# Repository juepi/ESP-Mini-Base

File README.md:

# ESP-Mini-Base
Base PCB ("hat") for ESP boards in WEMOS Mini format created with [KiCad EDA](https://www.kicad.org/). Primarily designed for [WEMOS S2 Mini](https://www.wemos.cc/en/latest/s2/s2_mini.html) and [D1 Mini](https://www.wemos.cc/en/latest/d1/d1_mini.html), might work for others / upcoming boards with a compatible pinout.  
The schematic describes the functionality and options in detail, it is also [available as PDF](pdf/ESP-Mini-Base_v1.0_schematic.pdf).

## Available functionality

The board provides the following functions:

* 3x N-Channel MOSFET drains (20A / 20Vds; no more than 5A recommended)
* 1x AC/DC SSR (48Vpp, 500mA max.)
* 1x Supply switch (5V or 3.3V, 2A max.)
* 2x 4-channel Level shifters to 5V
* 1x ADC attenuator with input selection (3V3 rail, 5V rail or external pin)
* 1x Pushbutton
* 3V3 and 5V I2C Pullups for default I2C pins of S2 and D1 Mini
* 5V LDO linear regulator for power supply up to 12V

The board has been designed in a way to allow you maximum flexibility. Every function needs to be enabled via solder jumpers on the bottom PCB side (for default wiring), or you may wire different IOs to the according pin headers on the board.  
The only exclusion are the 8 IOs wired to the 2 level shifters, which are hard wired and cannot be changed. The IOs have been selected to allow you level-shifted SPI or I2C for both S2 and D1 boards.

## Power Supply

There are several ways to power the board, the following table shows you the options and required configuration (solder jumpers on bottom PCB side):

| Powered by | Short Solder Jumpers | Notes |
| --- | --- | --- |
| 5V/VBUS Pin or USB Port | JP12 | Not recommended for MOSFET usage! At least connect GND wire to J9 if you try to do so|
| "12VDC" through J9 | JP12,JP13 | 5V generated from onboard regulator and supplied to ESP. Supported input voltage range: between 6.25 and 12V|
| 3.3VDC through J9 | none | Use to power ESP directly from LFP battery (in example)|

When powering the board from a LFP cell, you might want to have 5VDC (in example for a LED strip). Mainly for this reason, you have the ability to connect a Boost-converter board to J10. Short the Jumper JP11 and JP10 to 1-2 and you will be able to enable the Boost-converter via IO14 (U2 supply switch).  
Although the installed 5V LDO linear regulator supports up to 26V input voltage, no more than 12V are recommended due to the high power dissipation of the regulator.  

## Note on production data

The production data has been created for [JLCPCB assembly service](https://jlcpcb.com/) using the [Fabrication Toolkit Plugin](https://github.com/bennymeg/JLC-Plugin-for-KiCad). When placing an order, keep in mind that the rotation of several parts (MOSFETs, all ICs, C6) needs to be updated. Cross-check with the KiCAD Layout to verify that all parts will be placed correctly.

## Note on MOSFET usage

If you are switching a device through one of the 3 installed N-Channel MOSFETs, make sure that the switched device does **not have any reference to the input voltage GND** of the ESP-Mini-Base (in example through a data connection like I2C etc.). Chances are high to see magic smoke leaving your setup if you fail to use suitable galvanic isolation (beside the fact that the "switched" device probably won't power off at all)!
The MOSFETs have been tested fine with 5kHz PWM, so they should work for dimming RGB LED strips in example. Keep an eye on the overall current running through the FETs, more than 5A should be tested thoroughly before placing it into production.
  
## Pictures

Assembled ESP-Mini-Base v1.0 top side with S2 Mini  

Rendered view of the bottom side showing I/O and solder jumpers with descriptions.

**Note on I2C Pullup solder-jumpers (3,3 and 5V):** all 3 pins of the jumpers need to be connected with tin solder if you want to enable the pullups.

## ESPHome
Added sample ESPHome YAML config which uses most of the functionality provided by the ESP-Mini-Base. The sample is intended to be used with the `WEMOS S2 Mini` board.  
**Note on first wired flash:** The web based flashing with ESPHome did not work for me with the `WEMOS S2 Mini`. I had to download the compiled binary firmware and then used the [Adafruit WebSerial ESPTool](https://adafruit.github.io/Adafruit_WebSerial_ESPTool/) which managed to flash the ESP board correctly. Subsequent OTA updates worked perfectly well with ESPHome.

## Changelog

### v1.1
- Improved high current traces to MOSFETs
- Improved heat dissipation of LDO converter (IC1)
- Upgraded KiCAD files to version 8
- Set "remove from BoM" flag on all THT parts and solder jumpers

Have fun,  
Juergen

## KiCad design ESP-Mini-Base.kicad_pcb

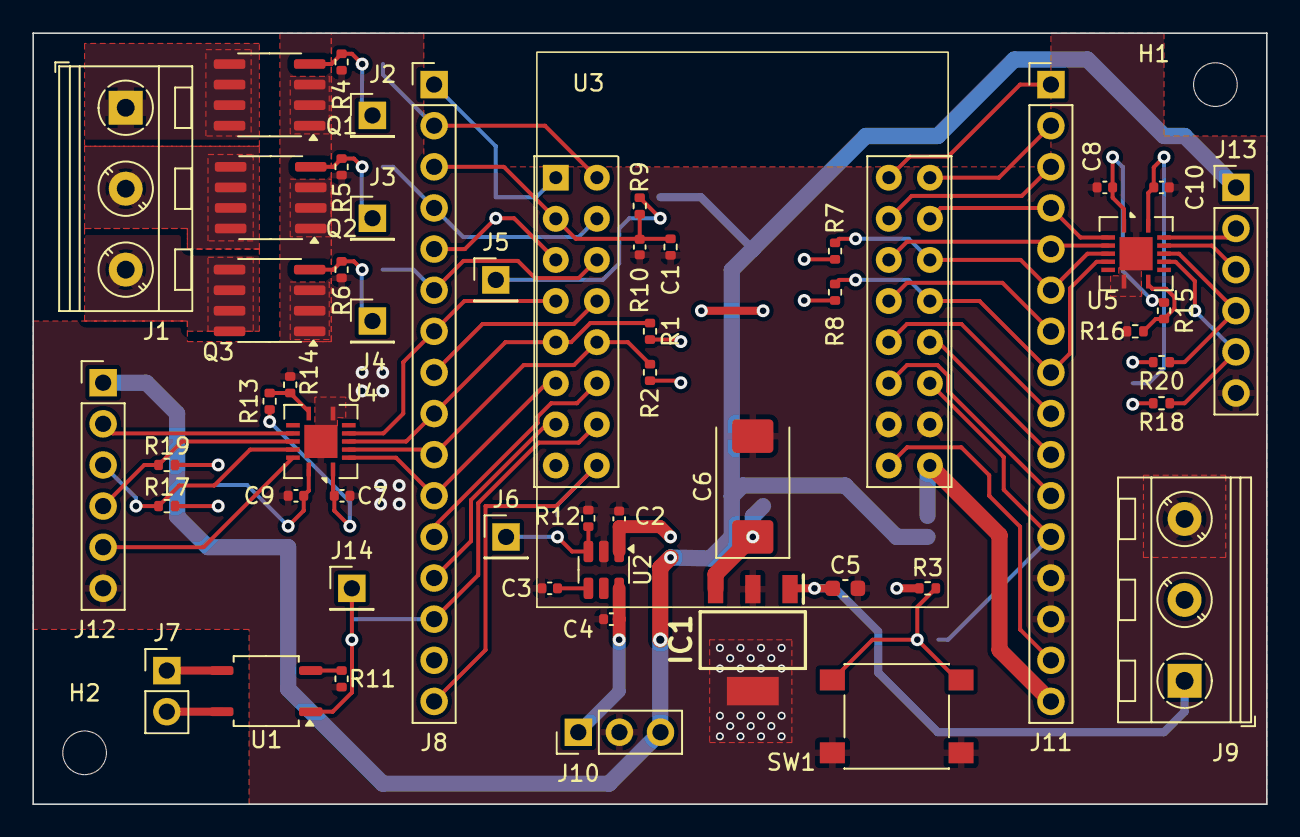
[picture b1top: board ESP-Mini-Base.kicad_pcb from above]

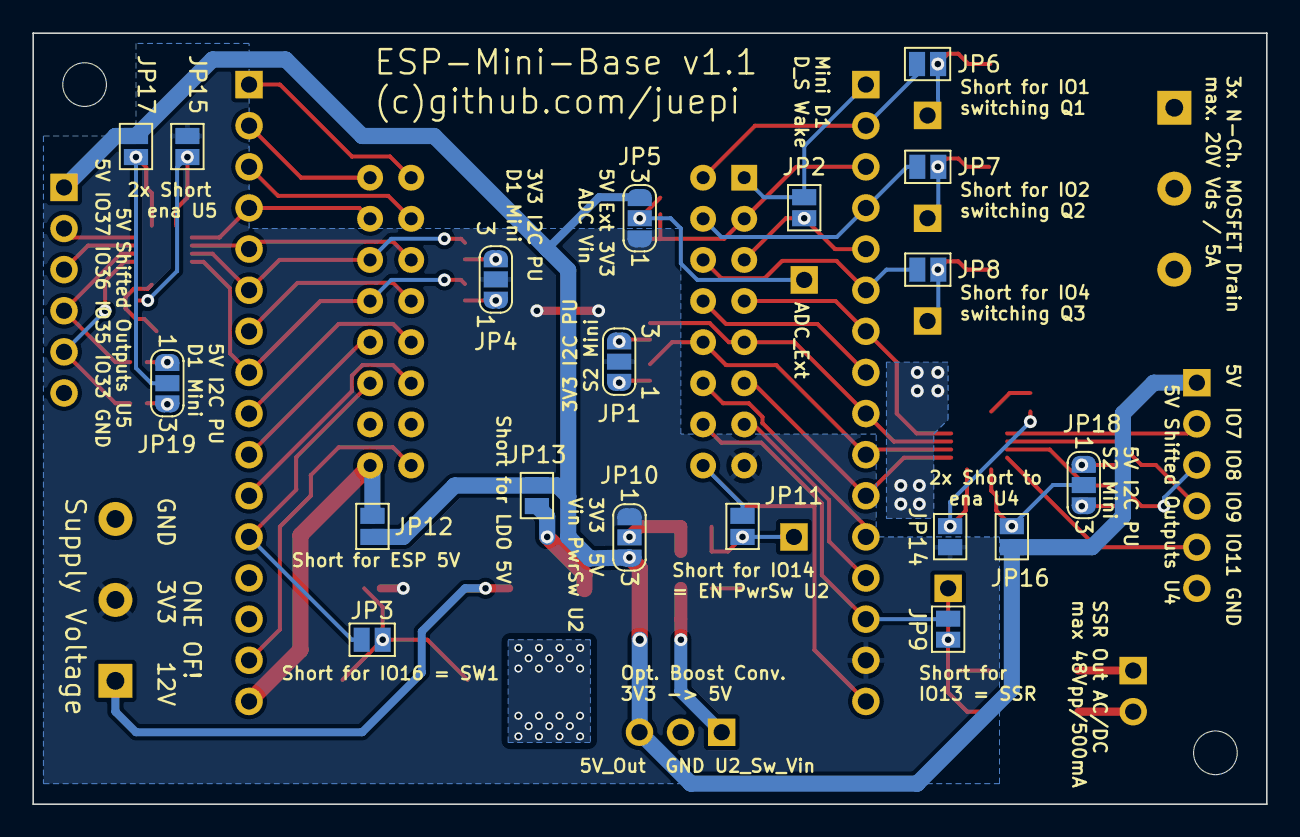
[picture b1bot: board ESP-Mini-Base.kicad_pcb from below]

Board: 2 copper layers, 76.2 x 47.6 mm, 75 parts (19 on the bottom side), 72 nets.

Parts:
C1, C4, C7, C8, C9, C10: 100n/25V; C_0402_1005Metric
C2: 1µ/25V; C_0402_1005Metric
C3: 1n/25V; C_0402_1005Metric
C5: 470nF/50V; C_0603_1608Metric
C6: 100µF/16V; CP_EIA-7343-31_Kemet-D
H1, H2: MountingHole; MountingHole_2.7mm_M2.5
IC1: LM2940IMP-5.0_NOPB; SOT230P700X180-4N
J1, J9: Screw_Terminal_01x03; TerminalBlock_RND_205-00046_1x03_P5.00mm_Horizontal
J2, J3, J4, J5, J6, J14: PinHeader_1x01_P2.54mm_Vertical
J7: Conn_01x02; PinHeader_1x02_P2.54mm_Vertical
J8, J11: Conn_01x16; PinHeader_1x16_P2.54mm_Vertical
J10: Conn_01x03; PinHeader_1x03_P2.54mm_Vertical
J12, J13: Conn_01x06; PinHeader_1x06_P2.54mm_Vertical
JP1, JP4, JP5, JP10, JP18, JP19: SolderJumper_3_Open; SolderJumper-3_P1.3mm_Open_RoundedPad1.0x1.5mm_NumberLabels
JP2, JP3, JP6, JP7, JP8, JP9, JP11, JP12, JP13, JP14, JP15, JP16, JP17: SolderJumper-2_P1.3mm_Open_Pad1.0x1.5mm
Q1, Q2, Q3: AO4402G; SOIC-8_3.9x4.9mm_P1.27mm
R1, R2, R7, R8: 3k3; R_0402_1005Metric
R3, R4, R5, R6, R12: 10k; R_0402_1005Metric
R9: 12k/0.1%; R_0402_1005Metric
R10: 3k6/0.1%; R_0402_1005Metric
R11: 220; R_0402_1005Metric
R13, R15: 931; R_0402_1005Metric
R14, R16: 1k8; R_0402_1005Metric
R17, R18, R19, R20: 4k7; R_0402_1005Metric
SW1: SW_Omron_B3FS; SW_Push_1P1T_NO_6x6mm_H9.5mm
U1: G3VM-61VY2; SOP-4_3.8x4.1mm_P2.54mm
U2: TPS22918DBVR; SOT-23-6
U3: S2 Mini; WEMOS_S2_Mini
U4, U5: TXB0104RGY; Texas_S-PVQFN-N14

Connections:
+3.3V: J8.15, J9.2, JP1.2 (C), JP4.2 (C), JP5.1 (A), JP10.1 (A), JP14.2 (B), JP15.2 (B), R3.2, U3.15 (3V3)
+5V: J10.3, J12.1, J13.1, JP5.3 (B), JP10.3 (B), JP12.1 (A), JP13.2 (B), JP16.2 (B), JP17.2 (B)
+12V: C5.1, IC1.1 (IN), J9.1
/EN: J8.1, JP2.2 (B), U3.1 (EN)
/IO1: J8.2, JP6.1 (A), U3.2 (IO1)
/IO2: J8.4, JP7.1 (A), U3.4 (IO2)
/IO3: C1.1, J8.3, R9.1, R10.2, U3.3 (IO3)
/IO4: J8.6, JP8.1 (A), U3.6 (IO4)
/IO5: J8.5, JP2.1 (A), U3.5 (IO5)
/IO6: J8.8, U3.8 (IO6)
/IO7: J8.7, U3.7 (IO7), U4.5 (A4)
/IO8: J8.10, R2.1, U3.10 (IO8), U4.3 (A2)
/IO9: J8.9, R1.1, U3.9 (IO9), U4.4 (A3)
/IO10: J8.12, U3.12 (IO10)
/IO11: J8.11, U3.11 (IO11), U4.2 (A1)
/IO12: J8.13, U3.13 (IO12)
/IO13: J8.14, JP9.1 (A), U3.14 (IO13)
/IO14: J8.16, JP11.1 (A), U3.16 (IO14)
/IO15: J11.15, U3.31 (IO15)
/IO16: J11.12, JP3.1 (A), U3.28 (IO16)
/IO17: J11.11, U3.27 (IO17)
/IO18: J11.10, U3.26 (IO18)
/IO21: J11.9, U3.25 (IO21)
/IO33: J11.8, R8.1, U3.24 (IO33), U5.5 (A4)
/IO34: J11.7, U3.23 (IO34)
/IO35: J11.6, R7.1, U3.22 (IO35), U5.4 (A3)
/IO36: J11.5, U3.21 (IO36), U5.3 (A2)
/IO37: J11.4, U3.20 (IO37), U5.2 (A1)
/IO38: J11.3, U3.19 (IO38)
/IO39: J11.2, U3.18 (IO39)
/IO40: J11.1, U3.17 (IO40)
GND: C1.2, C2.2, C3.2, C4.2, C5.2, C6.2, C7.2, C8.2, C9.2, C10.2, IC1.2 (GND_1), IC1.4 (GND_2), J9.3, J10.2, J11.13, J11.14, J12.6, J13.6, Q1.1 (S), Q1.2 (S), Q1.3 (S), Q2.1 (S), Q2.2 (S), Q2.3 (S), Q3.1 (S), Q3.2 (S), Q3.3 (S), R4.1, R5.1, R6.1, R10.1, R11.1, R12.1, R14.1, R16.1, SW1.1, U2.2 (GND), U3.29 (GND), U3.30 (GND), U4.7 (GND), U4.15 (Pad), U5.7 (GND), U5.15 (Pad)
unnamed: C6.1, IC1.3 (OUT), JP13.1 (A)
unnamed: J1.1, Q1.5 (D), Q1.6 (D), Q1.7 (D), Q1.8 (D)
unnamed: J1.2, Q2.5 (D), Q2.6 (D), Q2.7 (D), Q2.8 (D)
unnamed: J1.3, Q3.5 (D), Q3.6 (D), Q3.7 (D), Q3.8 (D)
unnamed: J2.1, JP6.2 (B), Q1.4 (G), R4.2
unnamed: J3.1, JP7.2 (B), Q2.4 (G), R5.2
unnamed: J4.1, JP8.2 (B), Q3.4 (G), R6.2
unnamed: J5.1, JP5.2 (C), R9.2
unnamed: J6.1, JP11.2 (B), R12.2, U2.3 (ON)
unnamed: J7.1, U1.3
unnamed: J7.2, U1.4
unnamed: C4.1, J10.1, U2.6 (VOUT)
unnamed: J11.16, JP12.2 (B), U3.32 (VBUS)
unnamed: J12.2, U4.10 (B4)
unnamed: J12.3, R17.1, U4.12 (B2)
unnamed: J12.4, R19.1, U4.11 (B3)
unnamed: J12.5, U4.13 (B1)
unnamed: J13.2, U5.13 (B1)
unnamed: J13.3, U5.12 (B2)
unnamed: J13.4, R20.1, U5.11 (B3)
unnamed: J13.5, R18.1, U5.10 (B4)
unnamed: J14.1, JP9.2 (B), U1.1
unnamed: JP1.1 (A), R2.2
unnamed: JP1.3 (B), R1.2
unnamed: JP3.2 (B), R3.1, SW1.2
unnamed: JP4.1 (A), R8.2
unnamed: JP4.3 (B), R7.2
unnamed: C2.1, JP10.2 (C), U2.1 (VIN)
unnamed: C7.1, JP14.1 (A), R13.2, U4.1 (VCCA)
unnamed: C8.1, JP15.1 (A), R15.2, U5.1 (VCCA)
unnamed: C9.1, JP16.1 (A), JP18.2 (C), U4.14 (VCCB)
unnamed: C10.1, JP17.1 (A), JP19.2 (C), U5.14 (VCCB)
unnamed: JP18.1 (A), R19.2
unnamed: JP18.3 (B), R17.2
unnamed: JP19.1 (A), R20.2
unnamed: JP19.3 (B), R18.2
unnamed: R11.2, U1.2
unnamed: C3.1, U2.4 (CT)
unnamed: R13.1, R14.2, U4.8 (OE)
unnamed: R15.1, R16.2, U5.8 (OE)

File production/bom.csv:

Designator,Footprint,Quantity,Value,LCSC Part #
"C1, C10, C4, C7, C8, C9",0402,6,100n/25V,C106256
C2,0402,1,1µ/25V,C967571
C3,0402,1,1n/25V,C575438
C5,0603,1,470nF/50V,C77572
C6,CP_EIA-7343-31_Kemet-D,1,100µF/16V,C171666
"H1, H2",MountingHole_2.7mm_M2.5,2,MountingHole,
IC1,SOT230P700X180-4N,1,LM2940IMP-5.0_NOPB,C13991
"J1, J9",TerminalBlock_RND_205-00046_1x03_P5.00mm_Horizontal,2,Screw_Terminal_01x03,
J10,PinHeader_1x03_P2.54mm_Vertical,1,Conn_01x03,
"J11, J8",PinHeader_1x16_P2.54mm_Vertical,2,Conn_01x16,
"J12, J13",PinHeader_1x06_P2.54mm_Vertical,2,Conn_01x06,
"J14, J2, J3, J4, J5, J6",PinHeader_1x01_P2.54mm_Vertical,6,~,
J7,PinHeader_1x02_P2.54mm_Vertical,1,Conn_01x02,
"JP1, JP10, JP18, JP19, JP4, JP5",SolderJumper-3_P1.3mm_Open_RoundedPad1.0x1.5mm_NumberLabels,6,SolderJumper_3_Open,
"JP11, JP12, JP13, JP14, JP15, JP16, JP17, JP2, JP3, JP6, JP7, JP8, JP9",SolderJumper-2_P1.3mm_Open_Pad1.0x1.5mm,13, ,
"Q1, Q2, Q3",SOIC-8_3.9x4.9mm_P1.27mm,3,AO4402G,C2931062
"R1, R2, R7, R8",0402,4,3k3,C965263
R10,0402,1,3k6/0.1%,C186338
R11,0402,1,220,C102889
"R12, R3, R4, R5, R6",0402,5,10k,C25744
"R13, R15",0402,2,931,C35293
"R14, R16",0402,2,1k8,C170383
"R17, R18, R19, R20",0402,4,4k7,C25900
R9,0402,1,12k/0.1%,C186350
SW1,SW_Push_1P1T_NO_6x6mm_H9.5mm,1,SW_Omron_B3FS,C271751
U1,SOP-4_3.8x4.1mm_P2.54mm,1,G3VM-61VY2,C1558855
U2,SOT-23-6,1,TPS22918DBVR,C131941
U3,WEMOS_S2_Mini,1,S2 Mini,
"U4, U5",Texas_S-PVQFN-N14,2,TXB0104RGY,C400708

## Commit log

2023-12-19 readme update
2023-12-22 added picture; updated readme
2023-12-22 update readme, pictures, schematic usage notes and pdf
2023-12-22 fixed typo
2024-03-10 minor improvements; updated to KiCAD 8
2026-04-26 added ESPHome yaml config
2026-04-26 update readme on wired ESPHome flashing
